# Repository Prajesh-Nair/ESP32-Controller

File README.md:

# J-Deck

<p align="center">
  <strong>An ESP32-C3 wireless controller for JATAYU and any Wi-Fi, Bluetooth, or ESP-NOW project.</strong><br />
  Compact in your hands. Fast on the link. Built to control.
</p>

<p align="center">

</p>

## Built for JATAYU. Ready for anything.

J-Deck is a purpose-built handheld wireless controller. Its primary role is to talk directly to the **JATAYU Flight Controller**, reading pilot inputs from twin analog joysticks and tactile controls before sending compact control data over **ESP-NOW**.

But it is not limited to flight. With its ESP32-C3 radio and programmable firmware, J-Deck can be adapted as a controller for robots, RC vehicles, smart-home projects, camera rigs, simulators, or any device that communicates through **Wi-Fi**, **Bluetooth Low Energy (BLE)**, or **ESP-NOW**.

No router is required for ESP-NOW. For other projects, choose the wireless mode and control protocol that best fits the device you are building.

> This repository contains the KiCad hardware design for the controller. Firmware, final protocol definitions, pin mappings, and flight-safety behaviour should be kept versioned alongside the matching JATAYU Flight Controller project.

## Wireless modes

| Mode | Great for | Typical connection |
| --- | --- | --- |
| ESP-NOW | Responsive device-to-device control, including JATAYU | Direct peer-to-peer packets; no access point required |
| Wi-Fi | Web dashboards, LAN-connected devices, and IoT projects | Connect through an access point or run a local access point |
| Bluetooth LE | Phones, tablets, and low-power nearby peripherals | BLE pairing and GATT services |

The controller hardware stays the same; the firmware defines the selected radio mode, packet format, mapping, and receiver behaviour.

## The link

```text
[J-Deck] -- ESP-NOW control packets --> [JATAYU Flight Controller]
[J-Deck] <-- optional telemetry ----- [JATAYU Flight Controller]
```

ESP-NOW is a strong fit for a dedicated RC link because it operates without a conventional Wi-Fi access point and keeps the radio exchange focused on the aircraft. The exact packet format, peer MAC addresses, update rate, channel, checksum, and failsafe timeout are firmware decisions - document them here when the flight stack is locked.

## Hardware

| Feature | Design choice |
| --- | --- |
| Brain | ESP32-C3-WROOM-02U - RISC-V MCU with 2.4 GHz radio |
| Flight controls | Two 2-axis analog joysticks |
| Extra input | Four tactile push buttons |
| Charging | USB-C input with TP4056 single-cell LiPo charger |
| Battery protection | DW01A + FS8205A protection stage |
| Regulation | AP2114H 3.3 V LDO |
| Feedback | Charge/status LEDs |

## Power

The controller is designed around a **single-cell 3.7 V LiPo battery**. USB-C feeds the onboard charger, while the battery protection circuit guards against over-charge, over-discharge, and over-current conditions. The 3.3 V regulator supplies the ESP32-C3 and controls.

**Treat lithium batteries with care:** use a protected, suitable 1S cell; inspect wiring and polarity before power-up; and never leave charging unattended.

## Repository map

```text
JATAYU-Controller.kicad_pro   KiCad project
JATAYU-Controller.kicad_sch   Schematic
JATAYU-Controller.kicad_pcb   PCB layout
JATAYU-Controller-BOM.csv     Bill of materials
GERBER/                       Manufacturing outputs
3D Files/                     Mechanical / enclosure assets
```

## Getting started

1. Open `JATAYU-Controller.kicad_pro` in KiCad.
2. Review the schematic, footprints, board rules, and antenna keep-out before ordering.
3. Generate fresh manufacturing files from the validated board revision.
4. Assemble and bring up the power rails first, then program and test the ESP-NOW firmware with the JATAYU Flight Controller.
5. Validate radio range, packet loss, neutral-stick calibration, arming logic, and failsafe behaviour **with props removed** before any flight test.

## Flight safety

This is an experimental flight-control device. A radio link must never be the only safety layer. The aircraft firmware should implement a conservative failsafe when packets stop arriving, reject malformed packets, require deliberate arming, and be tested in a controlled environment. Always follow applicable local regulations.

## Image checklist

The three placeholder images above are ready to be replaced with your own project shots:

1. A clean, assembled-controller hero photo.
2. An ESP-NOW architecture, telemetry, or range-test graphic.
3. A KiCad 3D render or close-up PCB photo.

---

<p align="center">Made for the <strong>JATAYU</strong> flight platform.</p>

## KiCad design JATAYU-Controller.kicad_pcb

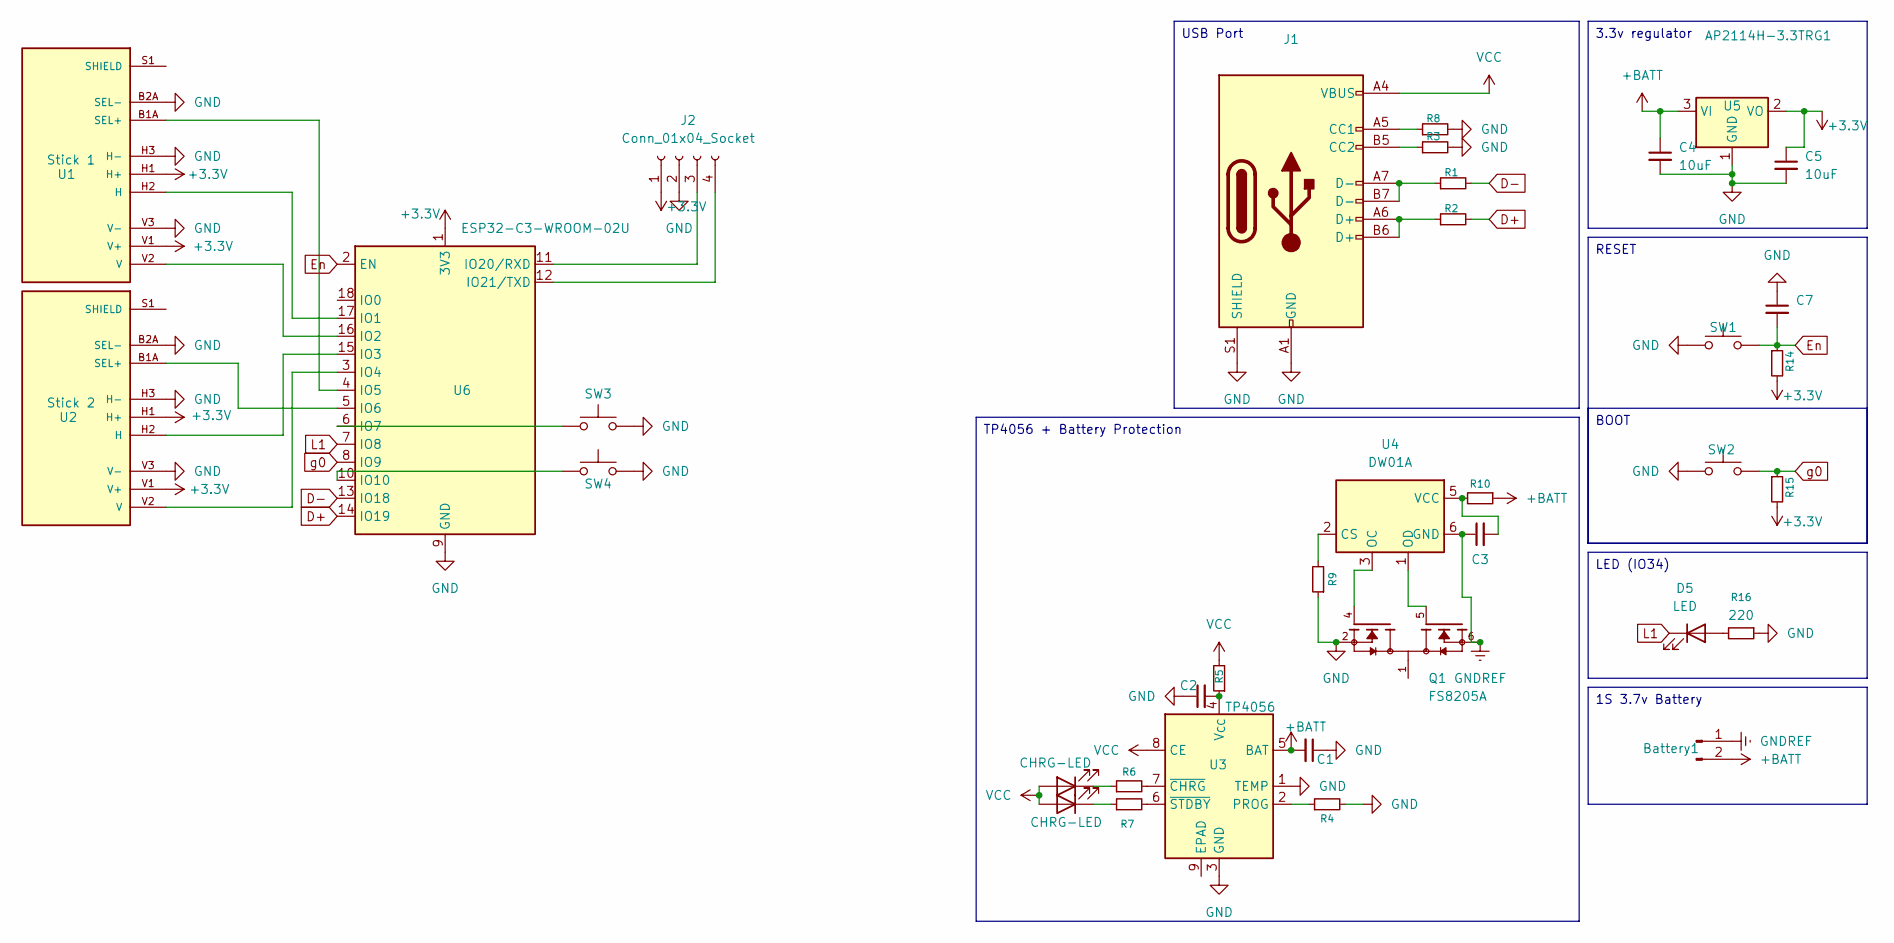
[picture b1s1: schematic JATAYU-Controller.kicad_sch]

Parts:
Battery1: Conn_01x02_Pin; PinHeader_1x02_P2.54mm_Vertical
C1, C2, C4, C5: 10uF; C_0603_1608Metric
C3: 0.1uF; C_0603_1608Metric
C7: 1uF; C_0603_1608Metric
D1, D2: CHRG-LED; LED_0805_2012Metric
D5: LED; LED_0805_2012Metric
J1: USB_C_Receptacle_USB2.0_14P; USB_C_Receptacle_GCT_USB4105-xx-A_16P_TopMnt_Horizontal
J2: Conn_01x04_Socket; PinSocket_1x04_P2.54mm_Vertical
Q1: FS8205A; SOP65P640X120-8N; PARTREV 1.7
R1, R2: 22; R_0603_1608Metric
R3, R8: 5.1K; R_0603_1608Metric
R4: 1.2K; R_0603_1608Metric
R5: 0.4; R_0603_1608Metric
R6, R7, R9: 1K; R_0603_1608Metric
R10: 100; R_0603_1608Metric
R14, R15: 10K; R_0603_1608Metric
R16: 220; R_0603_1608Metric
SW1, SW2, SW3, SW4: SW_Push; SW_Tactile_SPST_NO_Straight_CK_PTS636Sx25SMTRLFS
U1: Stick 1; XDCR_COM-09032; PARTREV N/A
U2: Stick 2; XDCR_COM-09032; PARTREV N/A
U3: TP4056; SOIC-8-1EP_3.9x4.9mm_P1.27mm_EP2.41x3.3mm_ThermalVias
U4: DW01A; SOT-23-6
U5: AP2114H-3.3TRG1; SOT-223-3_TabPin2
U6: ESP32-C3-WROOM-02U

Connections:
+3.3V: C5.1, J2.1, R14.2, R15.2, U1.H1 (H+), U1.V1 (V+), U2.H1 (H+), U2.V1 (V+), U5.2 (VO), U6.1 (3V3)
+BATT: Battery1.2, C1.2, C4.1, R10.1, U3.5 (BAT), U5.3 (VI); also elsewhere on the board
D+: R2.2, U6.14 (IO19)
D-: R1.2, U6.13 (IO18)
En: C7.2, R14.1, SW1.2, U6.2 (EN)
GND: C1.1, C2.1, C4.2, C5.2, C7.1, J1.A1 (GND), J1.A12 (GND), J1.B1 (GND), J1.B12 (GND), J1.S1 (SHIELD), J2.2, Q1.2, Q1.3, R3.2, R4.2, R8.2, R9.1, R16.1, SW1.1, SW2.1, SW3.2, SW4.2, U1.B2A (SEL-), U1.H3 (H-), U1.V3 (V-), U2.B2A (SEL-), U2.H3 (H-), U2.V3 (V-), U3.1 (TEMP), U3.3 (GND), U5.1 (GND), U6.9 (GND), U6.19 (GND)
GNDREF: Battery1.1, C3.1, Q1.6, Q1.7, U4.6 (GND); also elsewhere on the board
L1: D5.1 (K), U6.7 (IO8)
unnamed: D1.1 (K), R6.1
unnamed: D2.1 (K), R7.1
unnamed: D5.2 (A), R16.2
unnamed: J1.A5 (CC1), R8.1
unnamed: J1.B5 (CC2), R3.1
unnamed: J1.A6 (D+), J1.B6 (D+), R2.1
unnamed: J1.A7 (D-), J1.B7 (D-), R1.1
unnamed: J2.3, U6.11 (IO20/RXD)
unnamed: J2.4, U6.12 (IO21/TXD)
unnamed: Q1.1, Q1.8
unnamed: U1.H2 (H), U6.17 (IO1)
unnamed: U1.B1A (SEL+), U6.4 (IO5)
unnamed: U1.S1 (SHIELD), U1.S2 (SHIELD), U1.S3 (SHIELD), U1.S4 (SHIELD)
unnamed: U1.V2 (V), U6.16 (IO2)
unnamed: U2.H2 (H), U6.15 (IO3)
unnamed: U2.B1A (SEL+), U6.5 (IO6)
unnamed: U2.S1 (SHIELD), U2.S2 (SHIELD), U2.S3 (SHIELD), U2.S4 (SHIELD)
unnamed: U2.V2 (V), U6.3 (IO4)
unnamed: R4.1, U3.2 (PROG)
unnamed: C2.2, R5.1, U3.4 (V_{CC})
unnamed: R6.2, U3.7 (~CHRG)
unnamed: R7.2, U3.6 (~STDBY)
unnamed: R9.2, U4.2 (CS)
unnamed: Q1.4, U4.3 (OC)
unnamed: Q1.5, U4.1 (OD)
unnamed: C3.2, R10.2, U4.5 (VCC)
unnamed: SW3.1, U6.6 (IO7)
unnamed: SW4.1, U6.10 (IO10)
VCC: D1.2 (A), D2.2 (A), J1.A4 (VBUS), J1.A9 (VBUS), J1.B4 (VBUS), J1.B9 (VBUS), R5.2, U3.8 (CE)
g0: R15.1, SW2.2, U6.8 (IO9)

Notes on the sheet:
USB Port
TP4056 + Battery Protection
1S 3.7v Battery
RESET
BOOT
LED (IO34)
3.3v regulator

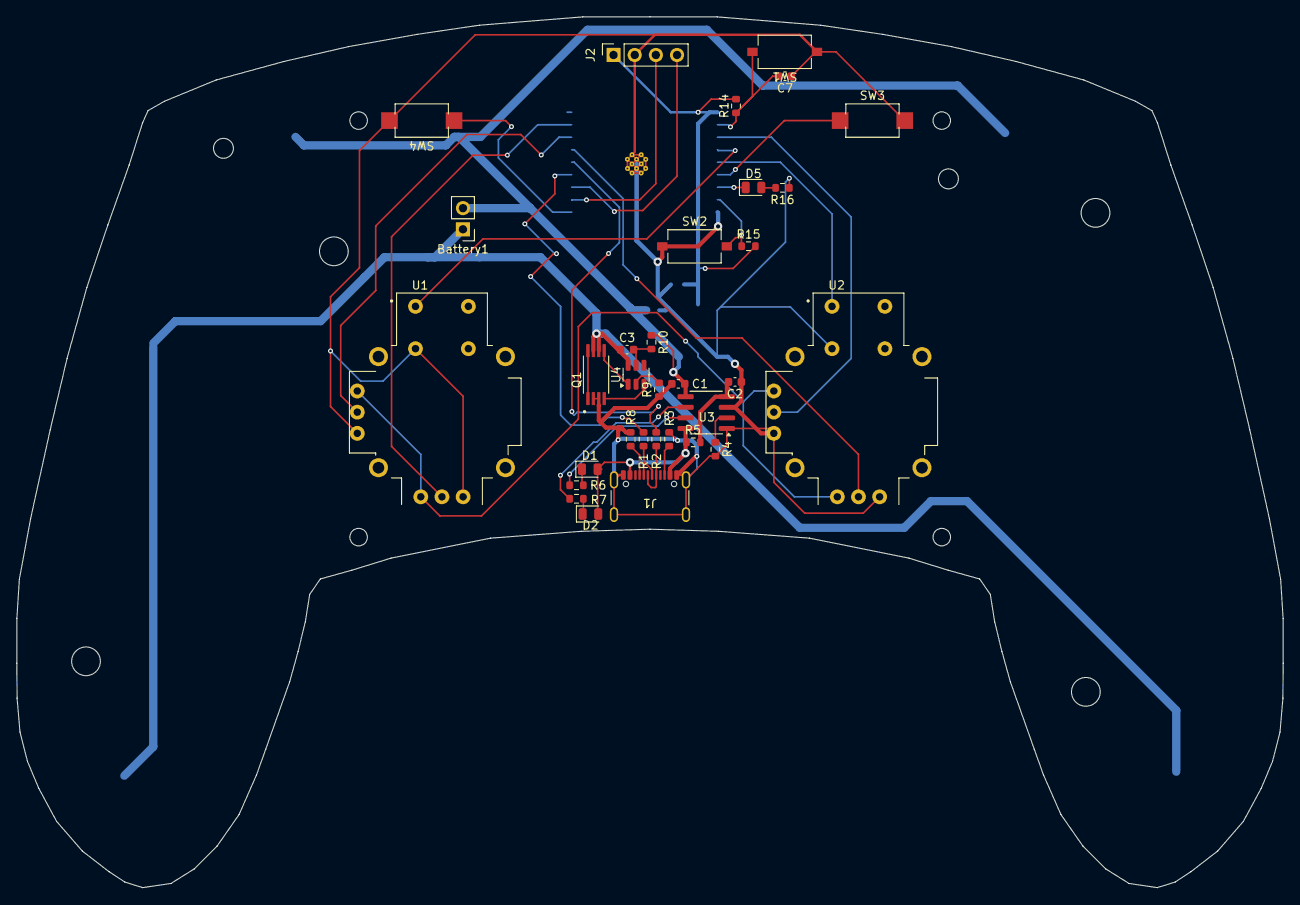
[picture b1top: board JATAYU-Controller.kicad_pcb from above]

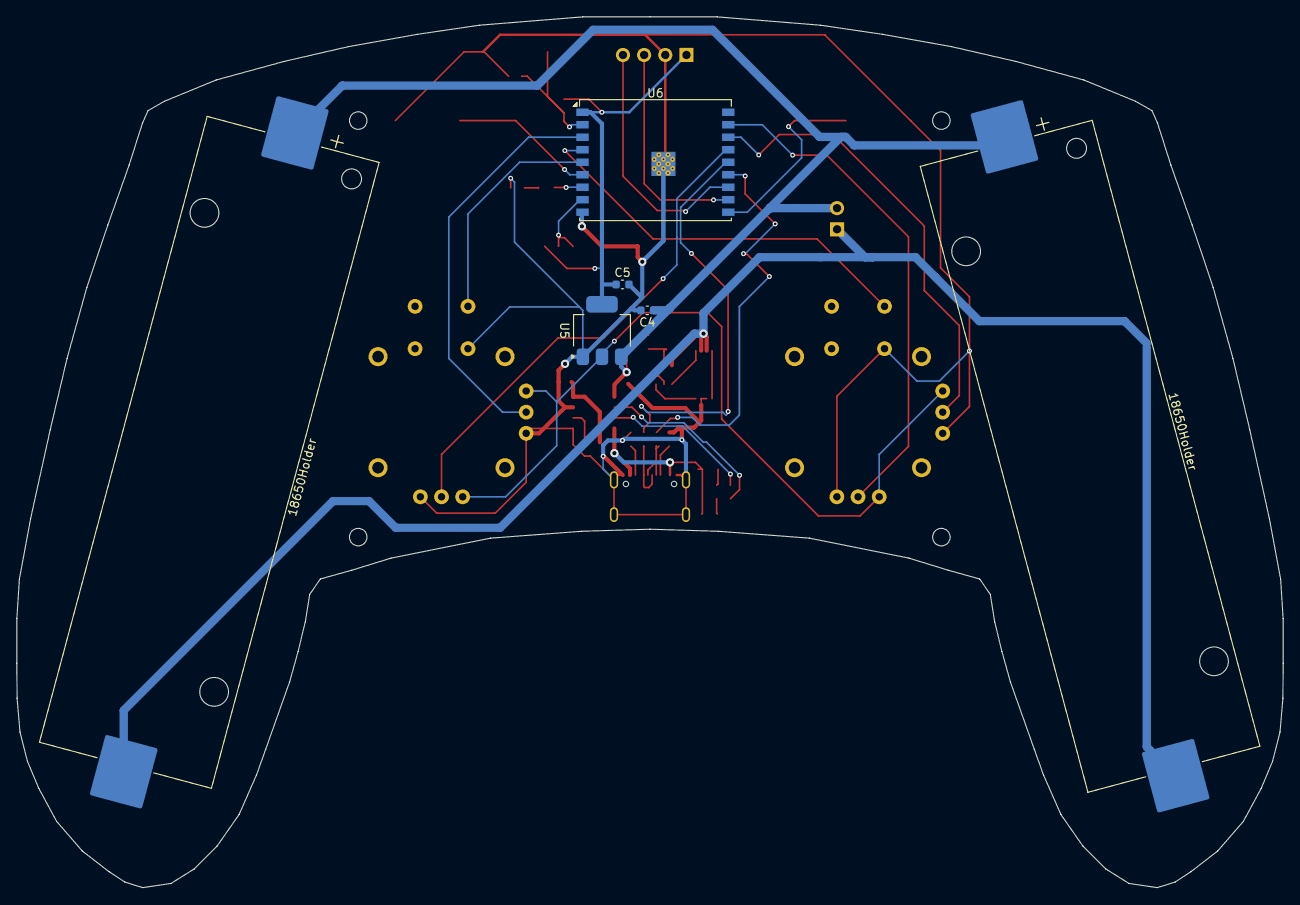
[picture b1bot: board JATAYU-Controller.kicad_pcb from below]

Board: 2 copper layers, 152.0 x 104.5 mm, 38 parts (6 on the bottom side), 38 nets.

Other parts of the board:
18650Holder, 18650Holder#2: 18650; BatteryHolder_Keystone_1042_1x18650

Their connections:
+BATT: 18650Holder.1, 18650Holder#2.1; also elsewhere on the board
GNDREF: 18650Holder.2, 18650Holder#2.2; also elsewhere on the board

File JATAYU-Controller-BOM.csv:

"Reference","Qty","Value","DNP","Exclude from BOM","Exclude from Board","Footprint","Datasheet"
"Battery1","1","Conn_01x02_Pin","","","","Connector_PinHeader_2.54mm:PinHeader_1x02_P2.54mm_Vertical","~"
"C1,C2,C4,C5","4","10uF","","","","Capacitor_SMD:C_0603_1608Metric","https://robu.in/product/0603x106m160nt-fh-16v-10uf-x5r%c2%b1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,~"
"C3","1","0.1uF","","","","Capacitor_SMD:C_0603_1608Metric","~"
"C7","1","1uF","","","","Capacitor_SMD:C_0603_1608Metric","https://robu.in/product/0603b105k160nt-fh-16v-1uf-x7r%c2%b11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"
"D1,D2","2","CHRG-LED","","","","LED_SMD:LED_0805_2012Metric","~"
"D5","1","LED","","","","LED_SMD:LED_0805_2012Metric","~"
"J1","1","USB_C_Receptacle_USB2.0_14P","","","","Connector_USB:USB_C_Receptacle_GCT_USB4105-xx-A_16P_TopMnt_Horizontal","https://robu.in/product/type-c-31-m-12-hroparts-5a-1-16p-fem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"
"J2","1","Conn_01x04_Socket","","","","Connector_PinSocket_2.54mm:PinSocket_1x04_P2.54mm_Vertical","~"
"Q1","1","FS8205A","","","","FS8205A:SOP65P640X120-8N",""
"R1,R2","2","22","","","","Resistor_SMD:R_0603_1608Metric","https://robu.in/product/ac0603fr-0722rl-yageo-res-thick-film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"
"R3,R8","2","5.1K","","","","Resistor_SMD:R_0603_1608Metric","https://robu.in/product/rt0603fre075k1l-yageo-100mw-thin-fil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"
"R4","1","1.2K","","","","Resistor_SMD:R_0603_1608Metric","~"
"R5","1","0.4","","","","Resistor_SMD:R_0603_1608Metric","~"
"R6,R7,R9","3","1K","","","","Resistor_SMD:R_0603_1608Metric","~"
"R10","1","100","","","","Resistor_SMD:R_0603_1608Metric","~"
"R14,R15","2","10K","","","","Resistor_SMD:R_0603_1608Metric","https://robu.in/product/ac0603fr-0710kl-yageo-res-thick-film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"
"R16","1","220","","","","Resistor_SMD:R_0603_1608Metric","~"
"SW1,SW2,SW3,SW4","4","SW_Push","","","","Button_Switch_SMD:SW_Tactile_SPST_NO_Straight_CK_PTS636Sx25SMTRLFS","https://robu.in/product/tsb008a2526a-bzcn-3-5mm-2-5mm-rectan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,~"
"U1","1","Stick 1","","","","COM-09032:XDCR_COM-09032",""
"U2","1","Stick 2","","","","COM-09032:XDCR_COM-09032",""
"U3","1","TP4056","","","","Package_SO:SOIC-8-1EP_3.9x4.9mm_P1.27mm_EP2.41x3.3mm_ThermalVias","https://www.lcsc.com/datasheet/lcsc_datasheet_2410121619_TOP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"
"U4","1","DW01A","","","","Package_TO_SOT_SMD:SOT-23-6","https://hmsemi.com/downfile/DW01A.PDF"
"U5","1","AP2114H-3.3TRG1","","","","Package_TO_SOT_SMD:SOT-223-3_TabPin2","https://www.lioncircuits.com/parts/AP2114H-3.3TRG1?srsltid=A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"
"U6","1","ESP32-C3-WROOM-02U","","","","RF_Module:ESP32-C3-WROOM-02U","https://www.espressif.com/sites/default/files/documentation/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"
